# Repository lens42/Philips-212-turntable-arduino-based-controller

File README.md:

# Philips-212-turntable-arduino-based-controller
A controller upgrade for the classic Philips 212 Hi-Fi turntable. Replaces all touch switch, motor control, and auto-off functions with an Arduino Uno clone
Files include Arduino sketch and KiCad files
Details at:  https://lensprojects.wordpress.com/2019/01/08/philips-212-turntable-controller-upgrade/

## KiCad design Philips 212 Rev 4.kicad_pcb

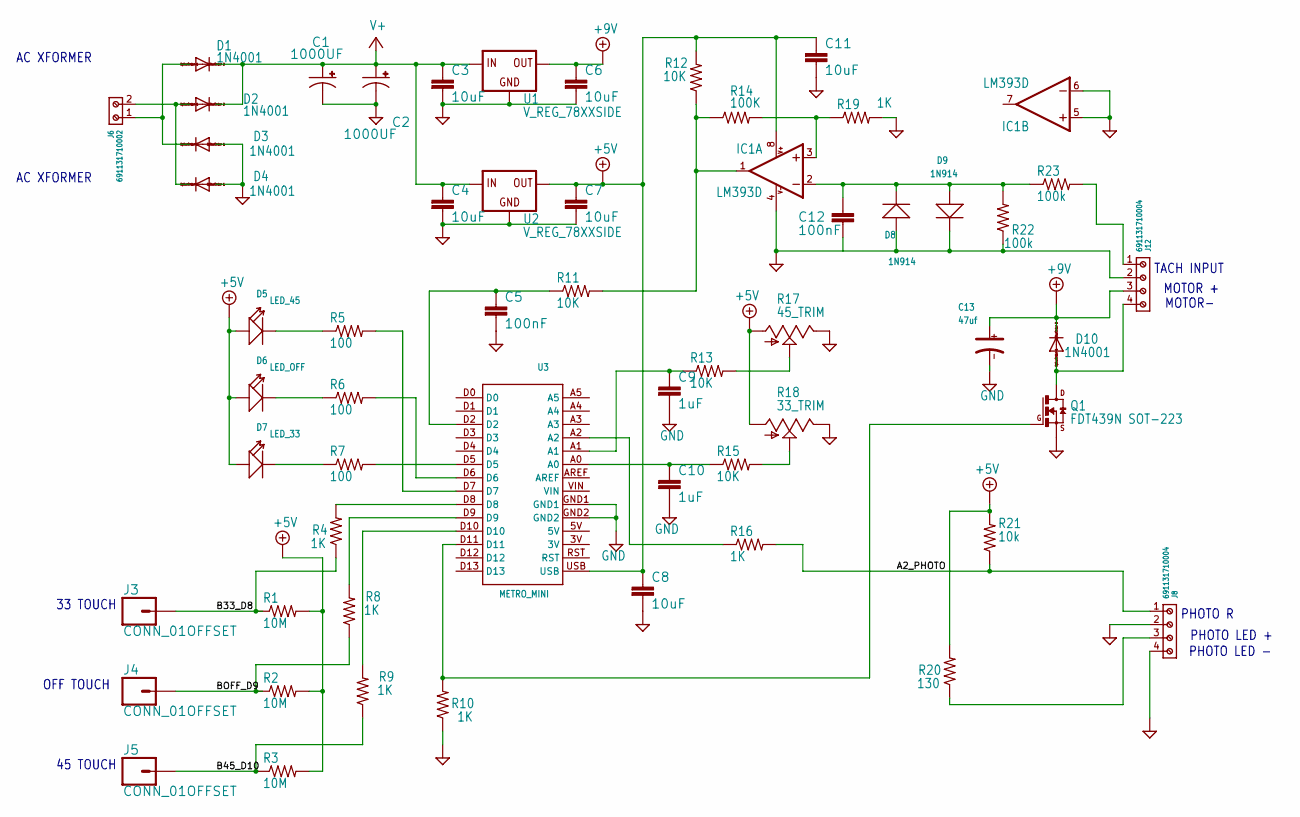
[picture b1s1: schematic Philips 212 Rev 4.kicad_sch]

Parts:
C1, C2: 1000UF; CAPPAD1700W60L1040D500P
C3, C4, C6, C7, C8, C11: 10uF; 1206
C5, C12: 100nF; 0805
C9, C10: 1uF; 1206
C13: 47uf; AVX-D
D1, D2, D3, D4, D10: 1N4001; DO41-10
D5: LED_45; LED2-2.54-D5.0MM
D6: LED_OFF; LED2-2.54-D5.0MM
D7: LED_33; LED2-2.54-D5.0MM
D8, D9: 1N914; DO-41
IC1: LM393D; SO08
J3, J4, J5: CONN_01OFFSET; 1X01_OFFSET
J6: 691131710002
J8, J12: 691131710004
Q1: FDT439N SOT-223; SOT-223
R1, R2, R3: 10M; M1206
R4, R8, R9, R10, R16, R19: 1K; M1206
R5, R6, R7: 100; M1206
R11, R12, R13, R15: 10K; M1206
R14: 100K; M1206
R17: 45_TRIM; PH212_POT
R18: 33_TRIM; PH212_POT
R20: 130; M1206
R21: 10k; M1206
R22, R23: 100k; M1206
U1, U2: V_REG_78XXSIDE; 78XXL
U3: METRO_MINI

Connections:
+5V: C7.1, C8.1, C11.1, D5.+, D6.+, D7.+, IC1.8 (V+), R1.2, R2.2, R3.2, R12.2, R17.1 (A), R18.1 (A), R20.2, R21.2, U2.OUT, U3.USB
+9V: C6.1, C13.+, D10.C, J12.3, U1.OUT
A0: R15.2, R18.2 (S)
A0N: C10.1, R15.1, U3.A0
A1: R13.2, R17.2 (S)
A1N: C9.1, R13.1, U3.A1
A2_PHOTO: J8.1, R16.2, R21.1
B33_D8: J3.1, R1.1, R4.1
B45_D10: J5.1, R3.1, R9.1
BOFF_D9: J4.1, R2.1, R8.1
CIN+: IC1.3 (+IN), R14.2, R19.1
CIN-: C12.1, D8.2 (-), D9.1 (+), IC1.2 (-IN), R22.2, R23.1
CMPOUT: IC1.1 (OUT), R11.2, R12.1, R14.1
D2: C5.1, R11.1, U3.D2
D8: R4.2, U3.D8
D9: R8.2, U3.D9
D10: R9.2, U3.D10
D10_GATE: Q1.1 (G), R10.2, U3.D11
GND: C1.2 (-), C2.2 (-), C3.2, C4.2, C5.2, C6.2, C7.2, C8.2, C9.2, C10.2, C11.2, C12.2, C13.-, D3.A, D4.A, D8.1 (+), D9.2 (-), IC1.4 (V-), IC1.5 (+IN), IC1.6 (-IN), J8.2, J8.4, J12.2, Q1.3 (S), R10.1, R17.3 (E), R18.3 (E), R19.2, R22.1, U1.GND, U2.GND, U3.GND1, U3.GND2
L33: D7.-, R7.1
L45: D5.-, R5.1
L45_D7: R5.2, U3.D7
LOFF: D6.-, R6.1
LOFF_D6: R6.2, U3.D6
MOTR-: D10.A, J12.4, Q1.2 (D), Q1.4 (D)
unnamed: R7.2, U3.D5
unnamed: R16.1, U3.A2
unnamed: J8.3, R20.1
unnamed: D1.A, D3.C, J6.1
unnamed: D2.A, D4.C, J6.2
TACH: J12.1, R23.2
V+: C1.1 (+), C2.1 (+), C3.1, C4.1, D1.C, D2.C, U1.IN, U2.IN

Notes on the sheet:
OFF TOUCH
PHOTO R
AC XFORMER
MOTOR +
MOTOR-
33 TOUCH
TACH INPUT
45 TOUCH
PHOTO LED -
PHOTO LED +

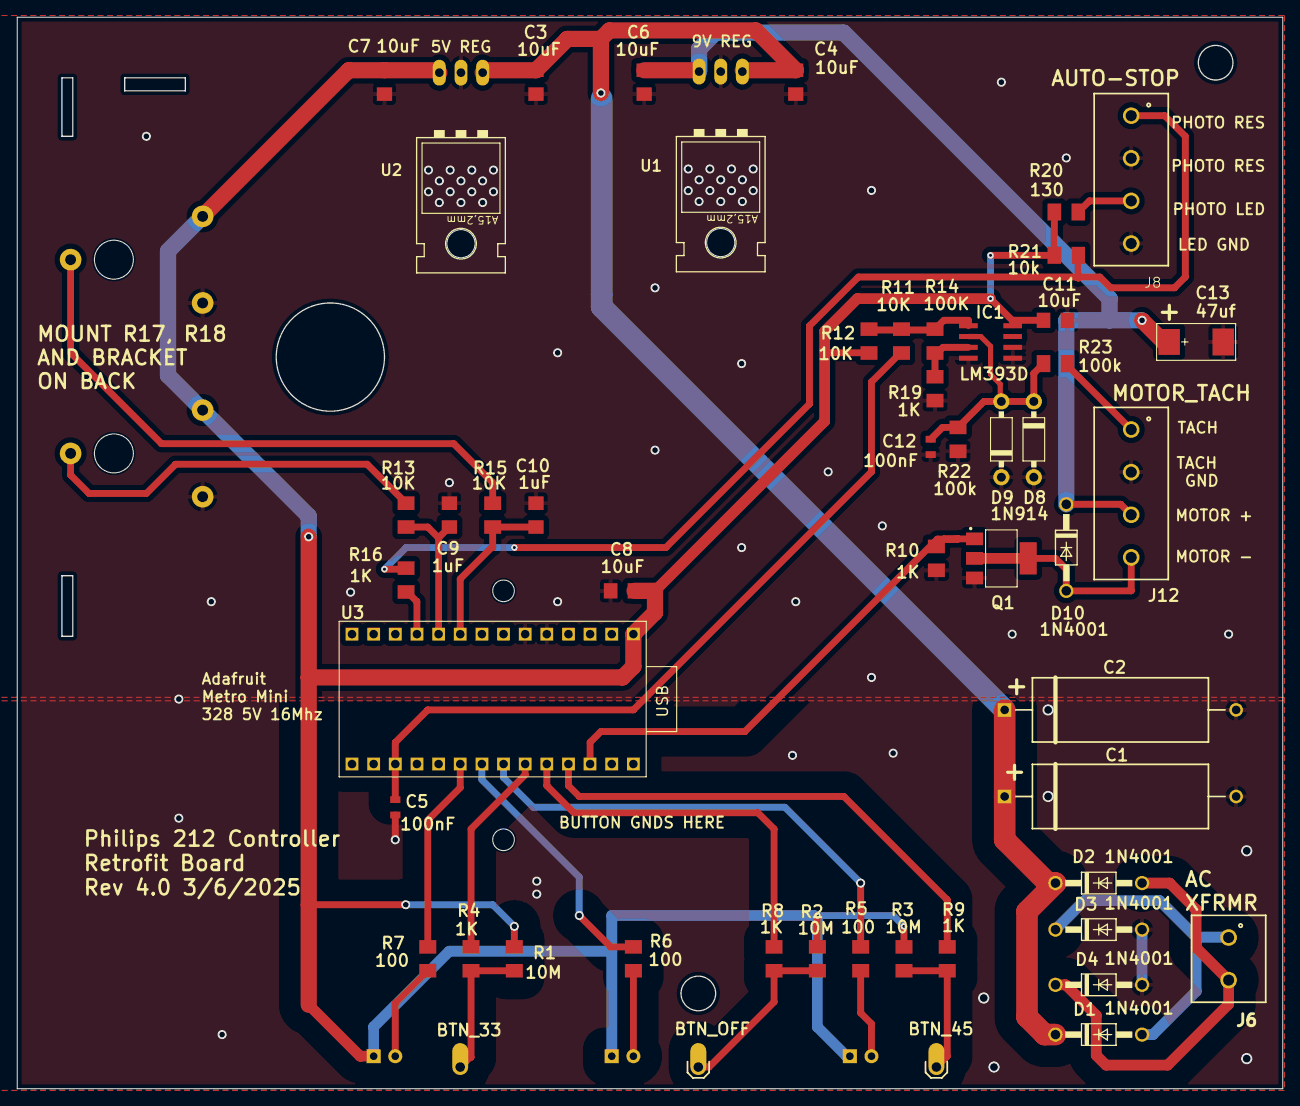
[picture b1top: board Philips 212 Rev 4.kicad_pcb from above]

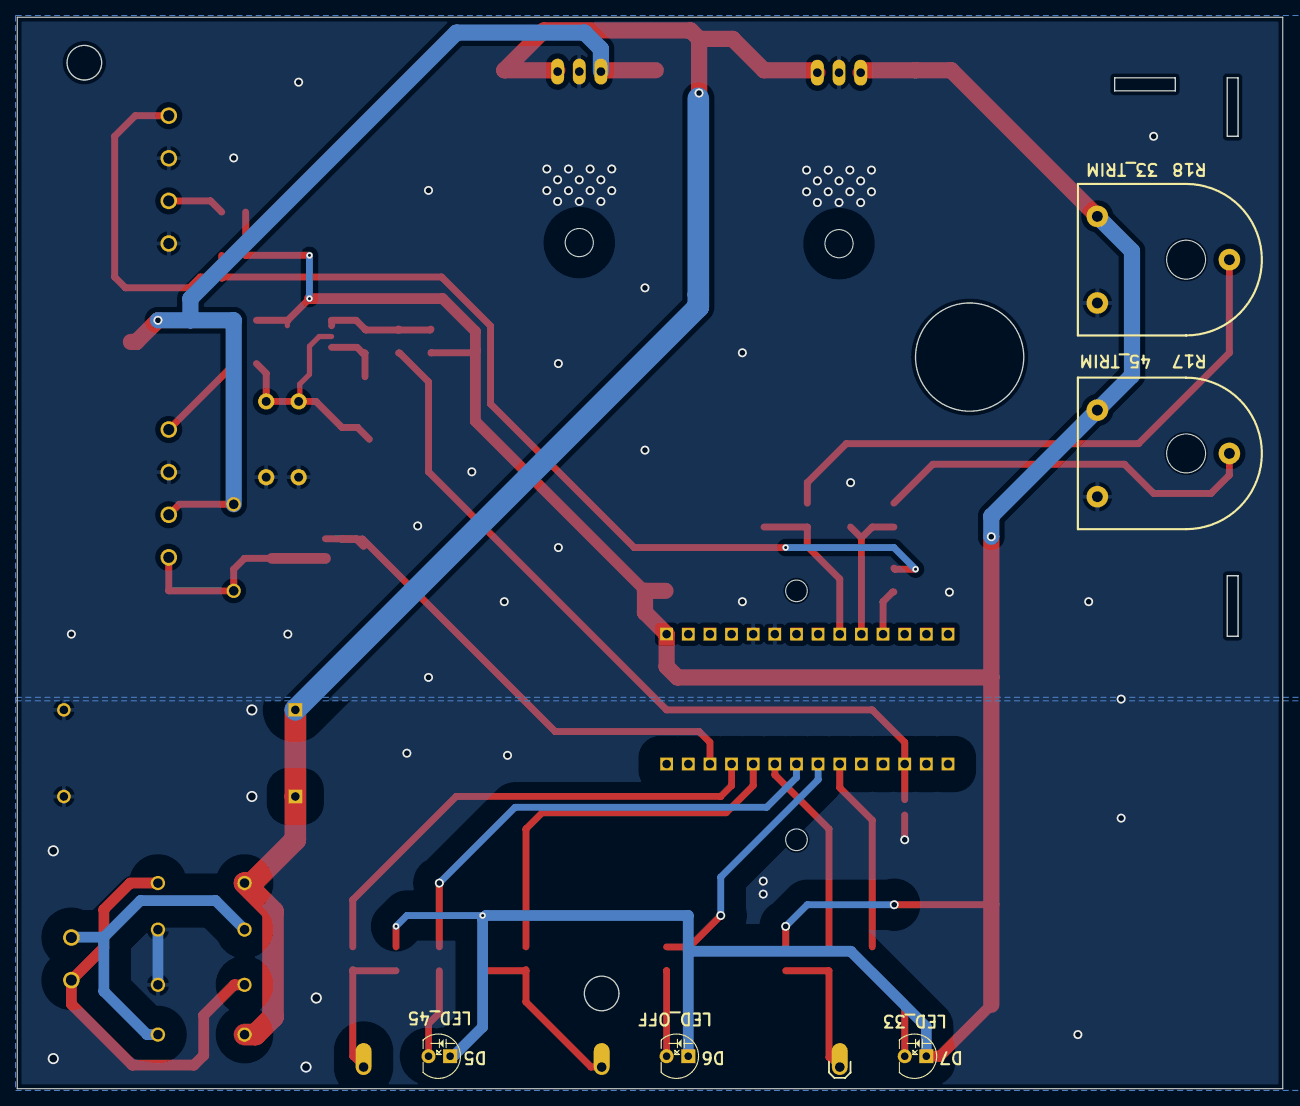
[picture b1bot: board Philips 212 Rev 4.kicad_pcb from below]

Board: 2 copper layers, 148.5 x 125.7 mm, 61 parts (6 on the bottom side), 32 nets.

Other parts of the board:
@HOLE0, @HOLE1, @HOLE2, @HOLE3: (no value)

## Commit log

2022-07-23 Adjust parameters for my GA-212
2022-07-25 Replace defines with const vars, improve photo trip logic to use change over time rather than min threshold
2022-07-25 PID WIP
2022-07-26 PID - WIP
2022-07-26 Working PID control
2022-07-26 Add trimmer logic
2022-07-26 Move consts
2022-07-26 Adjust target values to resemble RPMs, tidy up code
2022-07-27 Average out pidInput to prevent motor PWM oscillation
2022-07-27 Move velocity calculation outside of interrupt function
2022-07-27 Remove incorrect var assignment
2022-07-27 Set update rate of PWM value to ~500Hz, remove tach value averaging, increase motor startup time
2025-03-24 Add files via upload
    Rev 6 fixes a 45 RPM startup issues and some sloppy code
2025-03-24 Delete Phiips 212 r2.brd
    old version
2025-03-24 Delete Phiips 212 r3.brd
    old version
2025-03-24 Delete Phiips 212 r2.sch
    old version
2025-03-24 Delete Phiips 212 r3.sch
    old version
